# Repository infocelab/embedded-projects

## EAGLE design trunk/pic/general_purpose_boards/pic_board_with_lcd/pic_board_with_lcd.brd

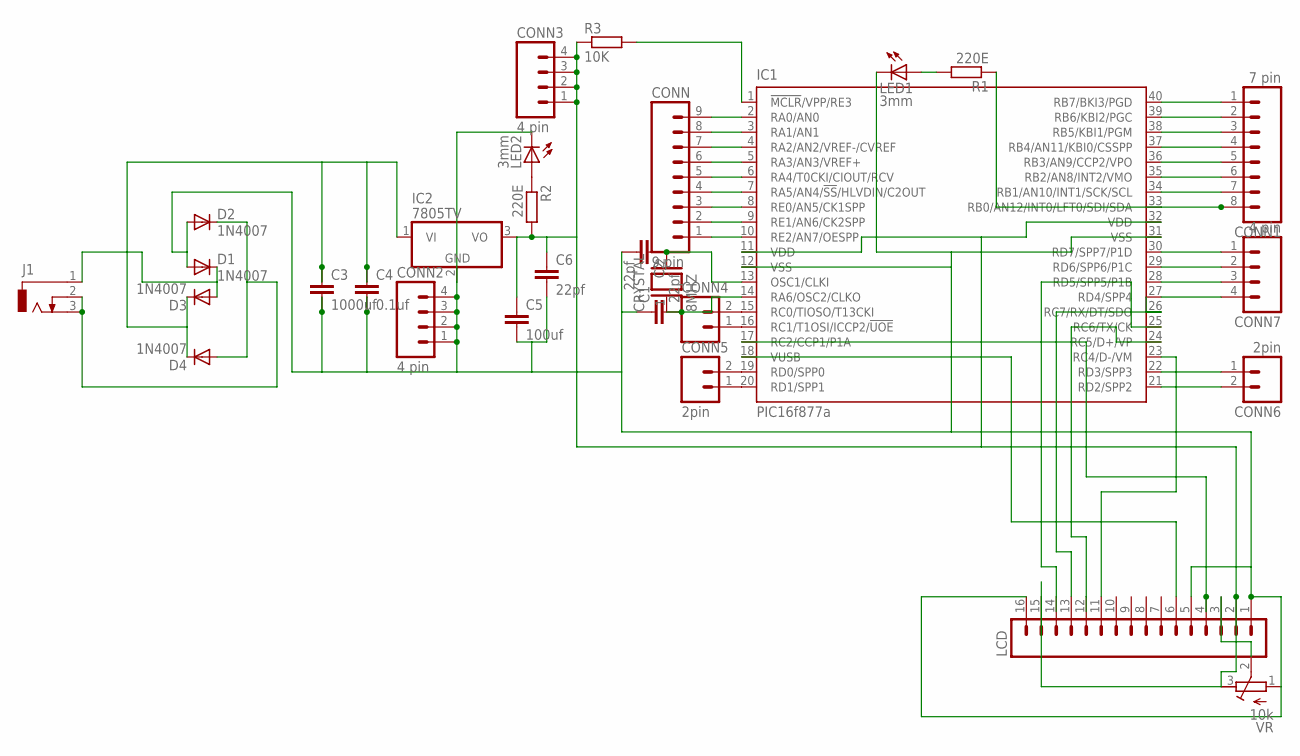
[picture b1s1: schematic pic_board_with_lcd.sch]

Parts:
C1, C2, C6: 22pf; C2.5-2
C3: 1000uf; C5B7.2
C4: 0.1uf; C2.5-3
C5: 100uf; C5B7.2
CONN: 9 pin; 09P
CONN1: 7 pin; 08P
CONN2, CONN3, CONN7: 4 pin; 04P
CONN4: M02; 02P
CONN5, CONN6: 2pin; 02P
CRYSTAL: 8MHZ; QS
D1, D2, D3, D4: 1N4007; DO41-10
IC1: PIC16f877a; DIL40
IC2: 7805TV; TO220V
J1: DCJ0303
LCD: M16; 16P
LED1, LED2: 3mm; LED3MM
R1, R2: 220E; 0204/7
R3: 10K; 0204/7
VR: 10k; RTRIM64P

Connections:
unnamed: C2.1, CRYSTAL.2, IC1.13 (OSC1/CLKI)
unnamed: C1.2, CRYSTAL.1, IC1.14 (RA6/OSC2/CLKO)
unnamed: LED1.A, R1.2
unnamed: CONN.1, IC1.10 (RE2/AN7/OESPP)
unnamed: CONN.2, IC1.9 (RE1/AN6/CK2SPP)
unnamed: CONN.3, IC1.8 (RE0/AN5/CK1SPP)
unnamed: CONN.4, IC1.7 (RA5/AN4/!SS!/HLVDIN/C2OUT)
unnamed: CONN.5, IC1.6 (RA4/T0CKI/CIOUT/RCV)
unnamed: CONN.6, IC1.5 (RA3/AN3/VREF+)
unnamed: CONN.7, IC1.4 (RA2/AN2/VREF-/CVREF)
unnamed: CONN.8, IC1.3 (RA1/AN1)
unnamed: CONN.9, IC1.2 (RA0/AN0)
unnamed: CONN5.1, IC1.20 (RD1/SPP1)
unnamed: CONN5.2, IC1.19 (RD0/SPP0)
unnamed: CONN4.1, IC1.16 (RC1/T1OSI/ICCP2/!UOE)
unnamed: CONN4.2, IC1.15 (RC0/TIOSO/T13CKI)
unnamed: IC1.17 (RC2/CCP1/P1A), LCD.4
unnamed: CONN6.1, IC1.22 (RD3/SPP3)
unnamed: CONN1.1, IC1.40 (RB7/BKI3/PGD)
unnamed: CONN1.2, IC1.39 (RB6/KBI2/PGC)
unnamed: CONN1.3, IC1.38 (RB5/KBI1/PGM)
unnamed: CONN1.4, IC1.37 (RB4/AN11/KBI0/CSSPP)
unnamed: CONN1.5, IC1.36 (RB3/AN9/CCP2/VPO)
unnamed: CONN1.6, IC1.35 (RB2/AN8/INT2/VMO)
unnamed: CONN1.7, IC1.34 (RB1/AN10/INT1/SCK/SCL)
unnamed: CONN6.2, IC1.21 (RD2/SPP2)
unnamed: CONN7.1, IC1.30 (RD7/SPP7/P1D)
unnamed: CONN7.2, IC1.29 (RD6/SPP6/P1C)
unnamed: CONN1.8, IC1.33 (RB0/AN12/INT0/LFT0/SDI/SDA), R1.1
unnamed: C3.1, C4.1, D3.C, D4.C, IC2.1 (VI)
unnamed: D2.C, D4.A, J1.2, J1.3
unnamed: D1.C, D3.A, J1.1
unnamed: C5.1, C6.1, CONN3.1, CONN3.2, CONN3.3, CONN3.4, IC1.11 (VDD), IC1.32 (VDD), IC2.3 (VO), LCD.2, LCD.15, R2.2, R3.1, VR.3 (A)
unnamed: LED2.A, R2.1
unnamed: C1.1, C2.2, C3.2, C4.2, C5.2, C6.2, CONN2.1, CONN2.2, CONN2.3, CONN2.4, D1.A, D2.A, IC1.12 (VSS), IC1.31 (VSS), IC2.2 (GND), LCD.1, LCD.5, LCD.16, LED1.K (C), LED2.K (C), VR.1 (E)
unnamed: CONN7.3, IC1.28 (RD5/SPP5/P1B)
unnamed: CONN7.4, IC1.27 (RD4/SPP4)
unnamed: IC1.23 (RC4/D-/VM), LCD.11
unnamed: IC1.1 (!MCLR!/VPP/RE3), R3.2
unnamed: LCD.3, VR.2 (S)
unnamed: IC1.24 (RC5/D+/VP), LCD.12
unnamed: IC1.25 (RC6/TX/CK), LCD.13
unnamed: IC1.26 (RC7/RX/DT/SDO), LCD.14
unnamed: IC1.18 (VUSB), LCD.6

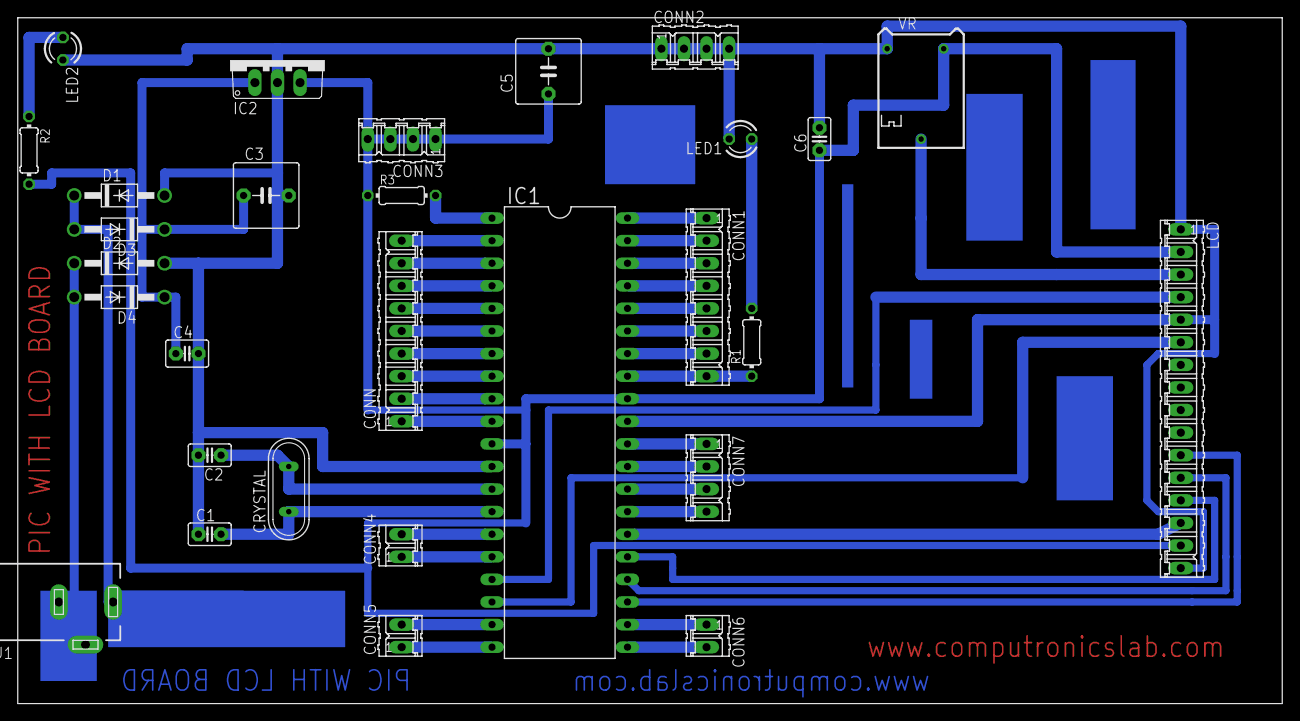
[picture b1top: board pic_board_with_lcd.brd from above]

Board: 2 copper layers, 142.2 x 77.1 mm, 29 parts (0 on the bottom side), 44 nets.
